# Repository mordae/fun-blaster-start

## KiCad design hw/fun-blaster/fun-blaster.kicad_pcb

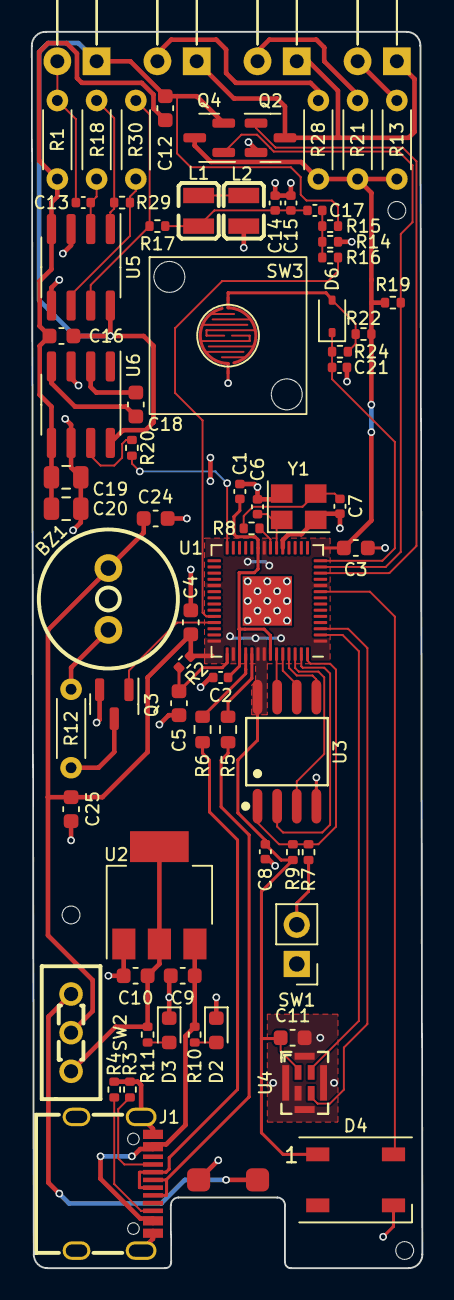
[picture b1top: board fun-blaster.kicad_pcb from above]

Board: 2 copper layers, 25.3 x 80.0 mm, 78 parts (1 on the bottom side), 54 nets.

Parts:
BT1: Battery; 2xAAA-Holder
BZ1: QMB-09B-03; BUZ-TH_BD9.0-P4.00-D0.6-FD
C1, C2, C8: 10u; C_0402_1005Metric
C3, C4, C5, C9, C10, C24, C25: 22u; C_0603_1608Metric
C6, C7: 30p; C_0402_1005Metric
C11, C12, C16, C18: 10u; C_0603_1608Metric
C13: 1u; C_0402_1005Metric
C14: 2.2n; C_0402_1005Metric
C15: 6.8n; C_0402_1005Metric
C17: 33n; C_0402_1005Metric
C19, C20: 22u; C_0805_2012Metric
C21: 1n; C_0402_1005Metric
D1, D5, D9: IR333-A; LED_D5.0mm_Horizontal_O6.35mm_Z3.0mm
D2: RED; D_0603_1608Metric
D3: GREEN; D_0603_1608Metric
D4: WS2812B; LED_WS2812B_PLCC4_5.0x5.0mm_P3.2mm
D6: 1N4148WS; D_SOD-323
H5, H7, H8: ToolingHole
J1: USB_C_Receptacle_USB2.0; USB-C_SMD-TYPE-C-31-M-12
L1, L2: 1mH; L1007
Q1: PT333-3B; LED_D5.0mm_Horizontal_O6.35mm_Z3.0mm
Q2, Q3: AO3400A; SOT-23
Q4: AO3401A; SOT-23
R1: 1k; R_Axial_DIN0204_L3.6mm_D1.6mm_P5.08mm_Horizontal
R2: 1; R_0402_1005Metric
R3, R4: 5.1k; R_0402_1005Metric
R5, R6: 27; R_0603_1608Metric
R7, R8, R17, R20, R29: 1k; R_0402_1005Metric
R9, R22, R24: 47k; R_0402_1005Metric
R10, R11, R16: 10k; R_0402_1005Metric
R12: 10; R_Axial_DIN0204_L3.6mm_D1.6mm_P5.08mm_Horizontal
R13, R21, R28: 22; R_Axial_DIN0204_L3.6mm_D1.6mm_P5.08mm_Horizontal
R14, R15: 2k; R_0402_1005Metric
R18, R30: 4.7k; R_Axial_DIN0204_L3.6mm_D1.6mm_P5.08mm_Horizontal
R19: 15k; R_0402_1005Metric
SW1: BOOT; PinHeader_1x02_P2.54mm_Vertical
SW2: SS-12D01-G3; SW-TH_DEALON_SS-12D01-GX
SW3: SW_SPST; RubberButton
U1: RP2040; QFN-56-1EP_7x7mm_P0.4mm_EP3.2x3.2mm
U2: AMS1117-3.3; SOT-223-3_TabPin2
U3: W25Q128JVS; SOIC-8_L5.3-W5.3-P1.27-LS8.0-BL
U4: GMA4030H11; MIC-SMD_8P-L3.0-W4.0-P0.85-BL
U5: LM2904; SOIC-8_3.9x4.9mm_P1.27mm
U6: ICL7660; SOIC-8_3.9x4.9mm_P1.27mm
Y1: X322512MSB4SI; Crystal_SMD_3225-4Pin_3.2x2.5mm

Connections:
+3V3: C10.1, R11.1, SW2.3 (C), U2.2 (VO)
+5V: C9.1, J1.A4 (VBUS), J1.A9 (VBUS), J1.B4 (VBUS), J1.B9 (VBUS), R10.2, U2.3 (VI)
+BATT: BT1.1 (+), SW2.1 (A)
/Audio/MIC_{clk}: U1.3 (GPIO1), U4.3 (CLOCK)
/Audio/MIC_{data}: U1.2 (GPIO0), U4.4 (DATA)
/Audio/buzzer: Q3.1 (G), U1.39 (GPIO27_ADC1)
/Controls/sw1: C21.2, D6.1 (K), R24.1, U1.14 (GPIO11)
/Controls/sw1-raw: D6.2 (A), R22.1, R24.2, SW3.2 (B)
/Light/IR_{en}: Q4.1 (G), R19.2, U1.13 (GPIO10)
/Light/IR_{osc}: R20.1, U1.28 (GPIO17)
/Light/IR_{rx}: R16.2, U1.38 (GPIO26_ADC0)
/Light/IR_{tx}: Q2.1 (G), U1.12 (GPIO9)
/Light/irvdd: C12.1, C16.1, Q1.1 (C), Q4.2 (S), R15.1, U5.8 (V+), U6.8 (V+)
/MCU/avdd: C5.1, R2.2, U1.43 (ADC_AVDD)
/MCU/d_usb+: J1.A6 (D+), J1.B6 (D+), R5.1
/MCU/d_usb-: J1.A7 (D-), J1.B7 (D-), R6.1
/MCU/dvdd: C1.1, C2.1, U1.23 (DVDD), U1.45 (VREG_VOUT), U1.50 (DVDD)
/MCU/flash_cs: R7.1, R9.2, U1.56 (QSPI_SS), U3.1 (~CS)
/MCU/flash_dio0: U1.53 (QSPI_SD0), U3.5 (DI(IO0))
/MCU/flash_dio1: U1.55 (QSPI_SD1), U3.2 (DO(IO1))
/MCU/flash_dio2: U1.54 (QSPI_SD2), U3.3 (IO2)
/MCU/flash_dio3: U1.51 (QSPI_SD3), U3.7 (IO3)
/MCU/flash_sclk: U1.52 (QSPI_SCLK), U3.6 (CLK)
/MCU/rgb-led: D4.4 (DIN), U1.9 (GPIO7)
/MCU/usb+: R5.2, U1.47 (USB_DP)
/MCU/usb-: R6.2, U1.46 (USB_DM)
GND: BT1.2 (-), C1.2, C2.2, C3.2, C4.2, C5.2, C6.1, C7.1, C8.2, C9.2, C10.2, C11.2, C14.2, C15.2, C19.2, C20.2, C21.1, C24.2, C25.2, D2.1 (K), D3.1 (K), D4.3 (VSS), J1.A1 (GND), J1.A12 (GND), J1.B1 (GND), J1.B12 (GND), J1.S1 (SHIELD), L2.2, Q2.2 (S), Q3.2 (S), R3.2, R4.2, R14.2, SW1.1 (A), SW3.1 (A), U1.19 (TESTEN), U1.57 (GND), U2.1 (GND), U3.4 (GND), U4.2 (RIGHT), U4.5 (GND), U4.6 (GND), U4.7 (GND), U4.8 (GND), U5.3 (+), U5.5 (+), U6.3 (GND), U6.6 (LV), Y1.2, Y1.4
unnamed: BZ1.2 (+), R12.1
unnamed: C7.2, R8.2, Y1.3
unnamed: C14.1, C15.1, C17.1, L1.1, R17.2
unnamed: C17.2, R14.1, R15.2, R16.1
unnamed: D1.2 (A), R13.2
unnamed: D1.1 (K), D5.1 (K), D9.1 (K), Q2.3 (D)
unnamed: D2.2 (A), R10.1
unnamed: D3.2 (A), R11.2
unnamed: D5.2 (A), R21.2
unnamed: D9.2 (A), R28.2
unnamed: J1.A5 (CC1), R3.1
unnamed: J1.B5 (CC2), R4.1
unnamed: L1.2, L2.1
unnamed: C13.1, Q1.2 (E), R1.1
unnamed: Q3.3 (D), R12.2
unnamed: R17.1, R30.2, U5.7
unnamed: R18.2, R29.1, U5.1
unnamed: R7.2, SW1.2 (B)
unnamed: C6.2, U1.20 (XIN), Y1.1
unnamed: R8.1, U1.21 (XOUT)
unnamed: C13.2, R18.1, U5.2 (-)
unnamed: R29.2, R30.1, U5.6 (-)
unnamed: C18.1, U6.2 (CAP+)
unnamed: C18.2, U6.4 (CAP-)
unnamed: R20.2, U6.7 (OSC)
VDD: BZ1.1 (-), C3.1, C4.1, C8.1, C11.1, C24.1, C25.1, D4.1 (VDD), Q4.3 (D), R2.1, R9.1, R13.1, R19.1, R21.1, R22.2, R28.1, SW2.2 (B), U1.1 (IOVDD), U1.10 (IOVDD), U1.22 (IOVDD), U1.33 (IOVDD), U1.42 (IOVDD), U1.44 (VREG_IN), U1.48 (USB_VDD), U1.49 (IOVDD), U3.8 (VCC), U4.1 (V_{DD})
VSS: C12.2, C16.2, C19.1, C20.1, R1.2, U5.4 (V-), U6.5 (VOUT)

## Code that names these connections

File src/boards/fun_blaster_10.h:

#pragma once

/* Delay to stabilize the oscillator. */
#if !defined(PICO_XOSC_STARTUP_DELAY_MULTIPLIER)
# define PICO_XOSC_STARTUP_DELAY_MULTIPLIER 64
#endif

/* QSPI flash access protocol selection. */
#define PICO_BOOT_STAGE2_CHOOSE_W25Q080 1
//#define PICO_BOOT_STAGE2_CHOOSE_GENERIC_03H 1

/* Flash access clock divider. */
#if !defined(PICO_FLASH_SPI_CLKDIV)
# define PICO_FLASH_SPI_CLKDIV 2
#endif

/* Total flash size in bytes. */
#if !defined(PICO_FLASH_SIZE_BYTES)
# define PICO_FLASH_SIZE_BYTES (16 * 1024 * 1024)
#endif

/* Buttons */
#define NUM_SWITCHES 1
#define SWITCH_PULL_UP 0
#define SWITCH_DEBOUNCE_US 0
#define SW1_PIN 11

/* IR */
#define IR_TX_PIN 9
#define IR_TX_SLICE 4
#define IR_TX_CHAN PWM_CHAN_B
#define IR_EN_PIN 10
#define IR_RX_PIN 26
#define IR_OSC_PIN 17
#define IR_OSC_SLICE 0
#define IR_OSC_CHAN PWM_CHAN_B

/* Buzzer */
#define BZ_PIN 27
#define BZ_SLICE 5
#define BZ_CHAN PWM_CHAN_B

/* Microphone */
#define MIC_DATA_PIN 0
#define MIC_CLK_PIN 1

/* WS2812B */
#define LED_PIN 7
#define LED_RED_MUL 1.0f
#define LED_GREEN_MUL 0.6f
#define LED_BLUE_MUL 2.0f

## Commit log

2023-06-17 Initial import
2023-06-18 Fix gitmodules urls
2023-06-18 Again
2023-06-18 Add udev rule
